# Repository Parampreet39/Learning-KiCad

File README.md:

# ⚡ Learning KiCad: Hardware & PCB Design

This repository documents my transition from "scrap" electronics to professional **Monozukuri** (craftsmanship). It contains my schematics, board layouts, and project evolution as I master the art of PCB design for IoT and Audio applications.

---

## 🏆 Featured Project: 5V to 3.3V Linear Regulator
My first complete PCB design focused on stable power delivery for microcontrollers.

### ✅ Key Features & Skills Demonstrated:
- **Schematic Capture:** Proper use of decoupling capacitors and power symbols.
- **Physical Layout:** Managed footprints for SMD (AMS1117-3.3) and Through-Hole components.
- **Thermal Management:** Implemented **Via Stitching** to dissipate heat between copper layers.
- **Signal Integrity:** Designed **Copper Pours (Ground Zones)** on both layers to minimize electrical noise.
- **Design Rule Check (DRC):** Optimized the layout to achieve **Zero Violations** and **Zero Unconnected Items**.
- **Branding:** Custom silkscreen art and QR code integration for documentation.

---

## 🛠️ The Roadmap
1. [x] **Basics:** Water Alarm

   V2 Modified it
    - **Added** : Cell Input , Diode for Reverse polarity protection , Potentiometer for Volume Change

---
**Designed by:** [Parampreet39](https://github.com/Parampreet39) | **Target:** Mechanical Engineering & IoT

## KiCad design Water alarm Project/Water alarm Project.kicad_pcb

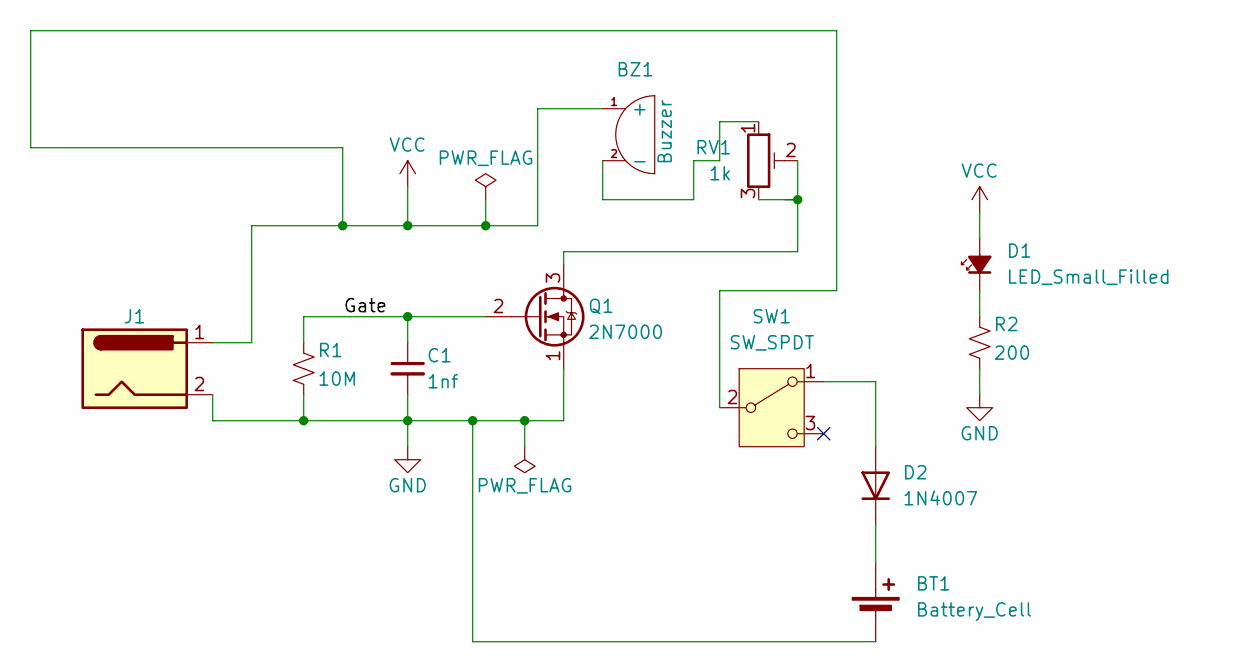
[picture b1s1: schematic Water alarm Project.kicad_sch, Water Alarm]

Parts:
BT1: Battery_Cell; BatteryHolder_Keystone_103_1x20mm
BZ1: Buzzer; Buzzer_D30mm_H20mm_P15mm__668-1652-ND__AI-3035-TT-12V-R
C1: 1nf; C_Disc_D3.0mm_W1.6mm_P2.50mm
D1: LED_Small_Filled; LED_D4.0mm
D2: 1N4007; D_DO-41_SOD81_P10.16mm_Horizontal
J1: Jack-DC; BarrelJack_GCT_DCJ200-10-A_Horizontal
Q1: 2N7000; TO-92_Inline
R1: 10M; R_Axial_DIN0204_L3.6mm_D1.6mm_P5.08mm_Horizontal
R2: 200; R_Axial_DIN0204_L3.6mm_D1.6mm_P5.08mm_Horizontal
RV1: 1k; Potentiometer_Bourns_3339P_Vertical_HandSoldering
SW1: SW_SPDT; SW_Slide_SPDT_Straight_CK_OS102011MS2Q

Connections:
/Gate: C1.1, Q1.2 (G), R1.1
GND: BT1.2 (-), C1.2, J1.2, Q1.1 (S), R1.2, R2.2
unnamed: BT1.1 (+), D2.1 (K)
unnamed: BZ1.2 (-), RV1.1
unnamed: D1.1 (K), R2.1
unnamed: D2.2 (A), SW1.1 (A)
unnamed: Q1.3 (D), RV1.2, RV1.3
VCC: BZ1.1 (+), D1.2 (A), J1.1, SW1.2 (B)

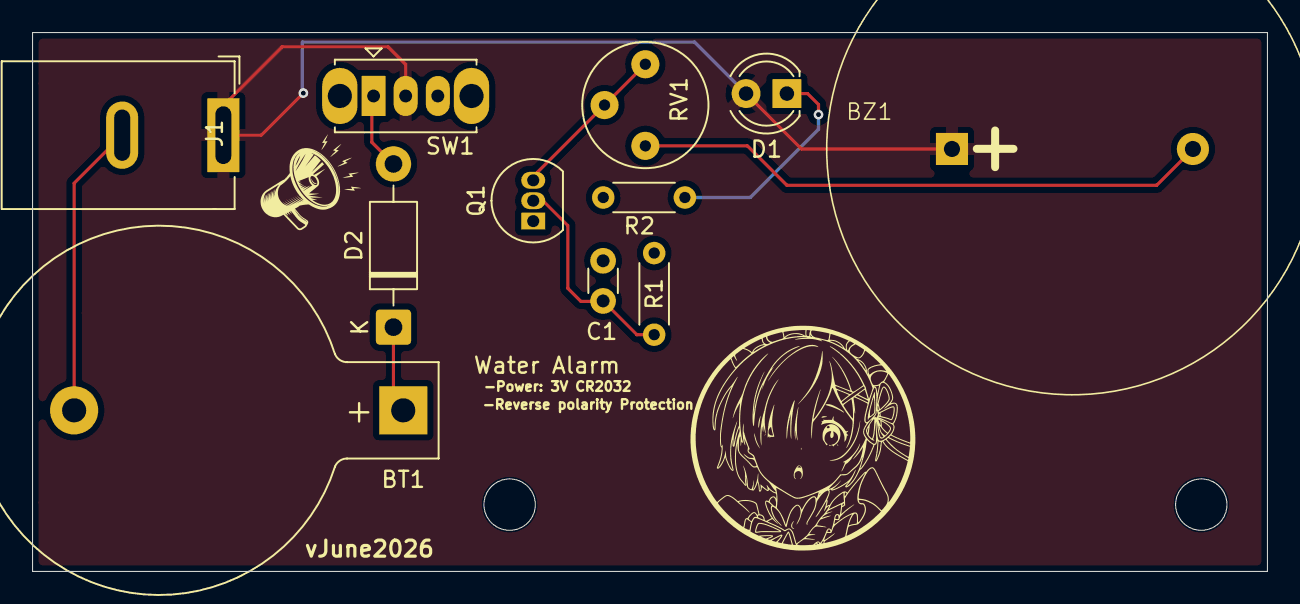
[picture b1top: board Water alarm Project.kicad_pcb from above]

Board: 2 copper layers, 76.9 x 33.6 mm, 11 parts (0 on the bottom side), 8 nets.

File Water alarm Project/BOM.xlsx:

Reference | Qty | Value | DKPN
BT1 | 1 | Battery_Cell | 277-1247-ND
BZ1 | 1 | Buzzer | 668-1652-ND
C1 | 1 | 1nf | 56-K102K10X7RH5UL2CT-ND
D1 | 1 | LED_Small_Filled | 67-1102-ND
D2 | 1 | 1N4007 | 641-1312-1-ND
J1 | 1 | Jack-DC | CP-037A-ND
Q1 | 1 | 2N7000 | 4878-2N7000CT-ND
R1 | 1 | 10M | CF18JT10M0CT-ND
R2 | 1 | 200 | CF14JT200RCT-ND
RV1 | 1 | 1k | Potentiometer_THT:Potentiometer_Bourns_3362P_Vertical
SW1 | 1 | SW_SPDT | EG1218

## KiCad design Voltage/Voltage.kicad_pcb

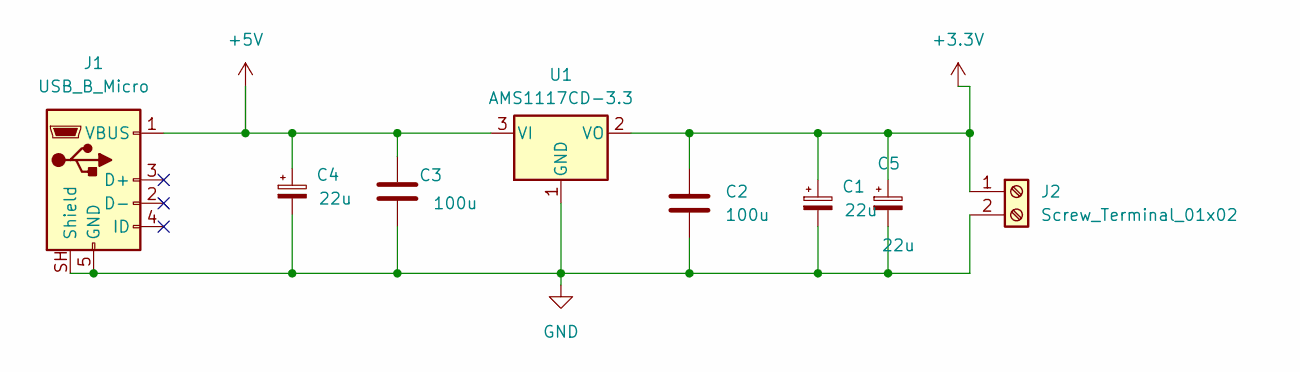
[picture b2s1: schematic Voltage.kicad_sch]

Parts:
C1, C4, C5: 22u; CP_Elec_6.3x7.7
C2, C3: 100u; C_0402_1005Metric
J1: USB_B_Micro; USB_Micro-B_Molex_47346-0001
J2: Screw_Terminal_01x02; TerminalBlock_Phoenix_MKDS-3-2-5.08_1x02_P5.08mm_Horizontal
U1: AMS1117CD-3.3; TO-252-3_TabPin2

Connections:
+3.3V: C1.1, C2.1, C5.1, J2.1, U1.2 (VO)
+5V: C3.1, C4.1, J1.1 (VBUS), U1.3 (VI)
GND: C1.2, C2.2, C3.2, C4.2, C5.2, J1.5 (GND), J1.SH (Shield), J2.2, U1.1 (GND)

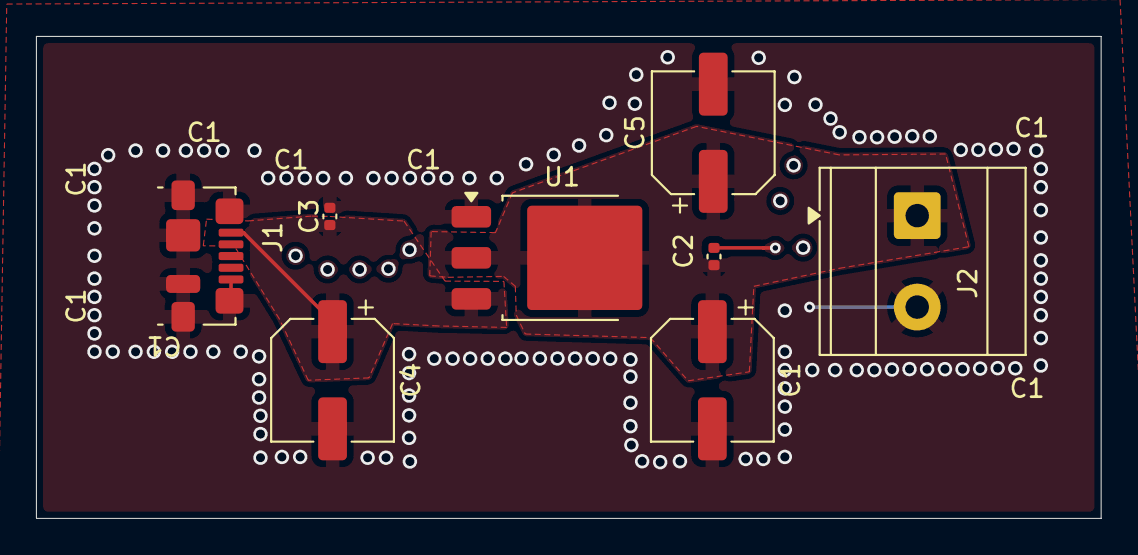
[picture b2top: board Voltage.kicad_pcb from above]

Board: 2 copper layers, 59.1 x 26.8 mm, 8 parts (0 on the bottom side), 3 nets.

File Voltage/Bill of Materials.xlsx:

Id | Designator | Footprint | Quantity | Designation | Supplier and ref | Column1 | _1
1 | C1, C4, C5 | CP_Elec_6.3x7.7 | 3 | 22u
2 | C2, C3 | C_0402_1005Metric | 2 | 100u
3 | J1 | USB_Micro-B_Molex_47346-0001 | 1 | USB_B_Micro
4 | J2 | TerminalBlock_Phoenix_MKDS-3-2-5.08_1x02_P5.08mm_Horizontal | 1 | Screw_Terminal_01x02
5 | U1 | TO-252-3_TabPin2 | 1 | AMS1117CD-3.3

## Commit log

2026-05-17 feat: Complete 5V to 3.3V Regulator PCB with Zero DRC Errors
    - Implemented via stitching for thermal relief on AMS1117.
    - Verified zero unconnected items and zero design violations.
    - Added custom silkscreen branding and QR code.
    - Added Ton of Vias for clean signal
2026-05-23 Complete Voltage converter added bill of materials
2026-05-24 Completed
2026-05-25 Water Buzzer project start
2026-05-25 I worked on the pcb file for hours to find the kicad to crash and lost all my pcb files
2026-05-25 Finally Pcb done now adding imags etc
2026-05-25 complete water alarm doing final jobs
2026-05-25 Added gerber files and plots
2026-05-25 Some changes
2026-05-26 Updated the Water alarm added new parts
2026-05-26 Modified gerber files and pngs
2026-06-06 SOme minor changes
2026-06-13 Some fixes
